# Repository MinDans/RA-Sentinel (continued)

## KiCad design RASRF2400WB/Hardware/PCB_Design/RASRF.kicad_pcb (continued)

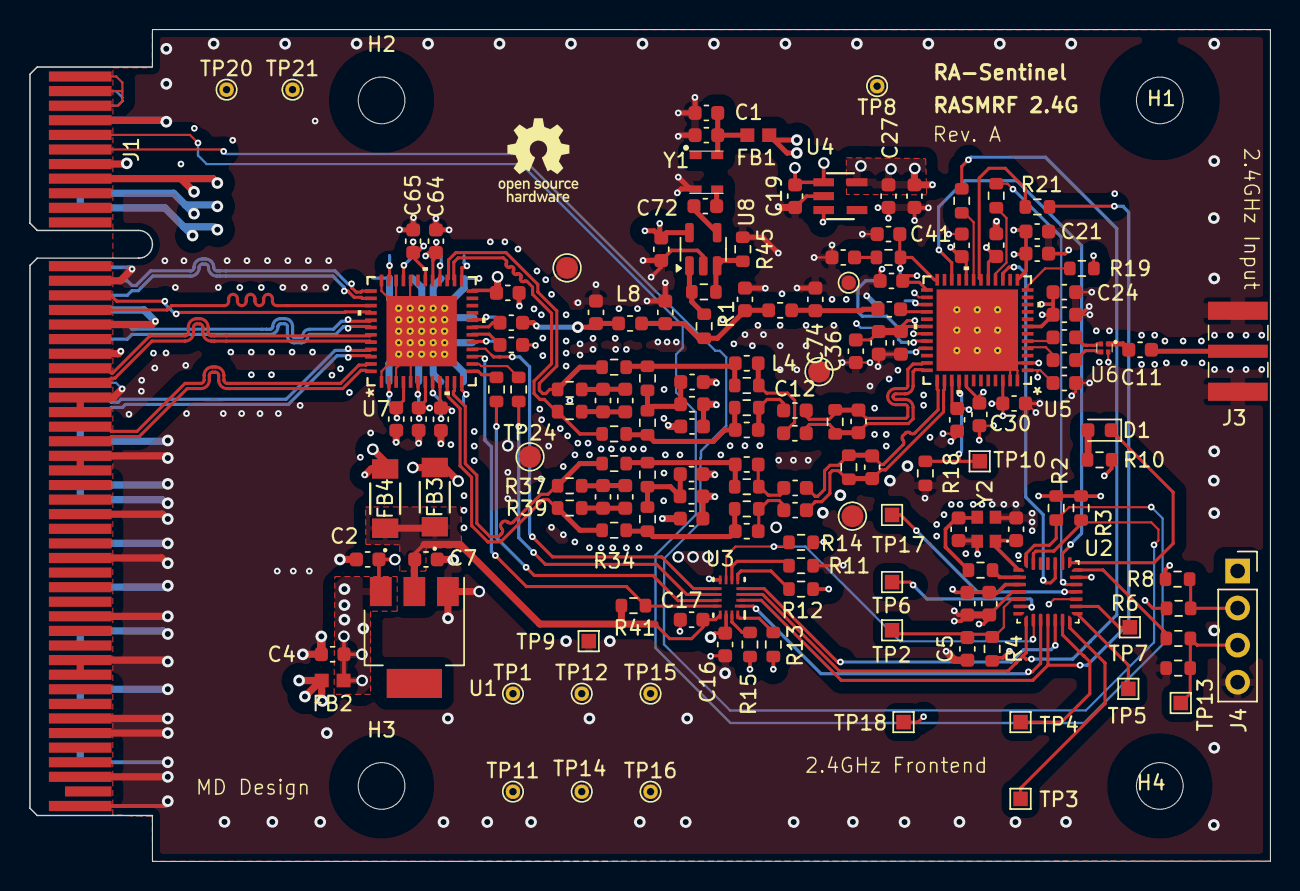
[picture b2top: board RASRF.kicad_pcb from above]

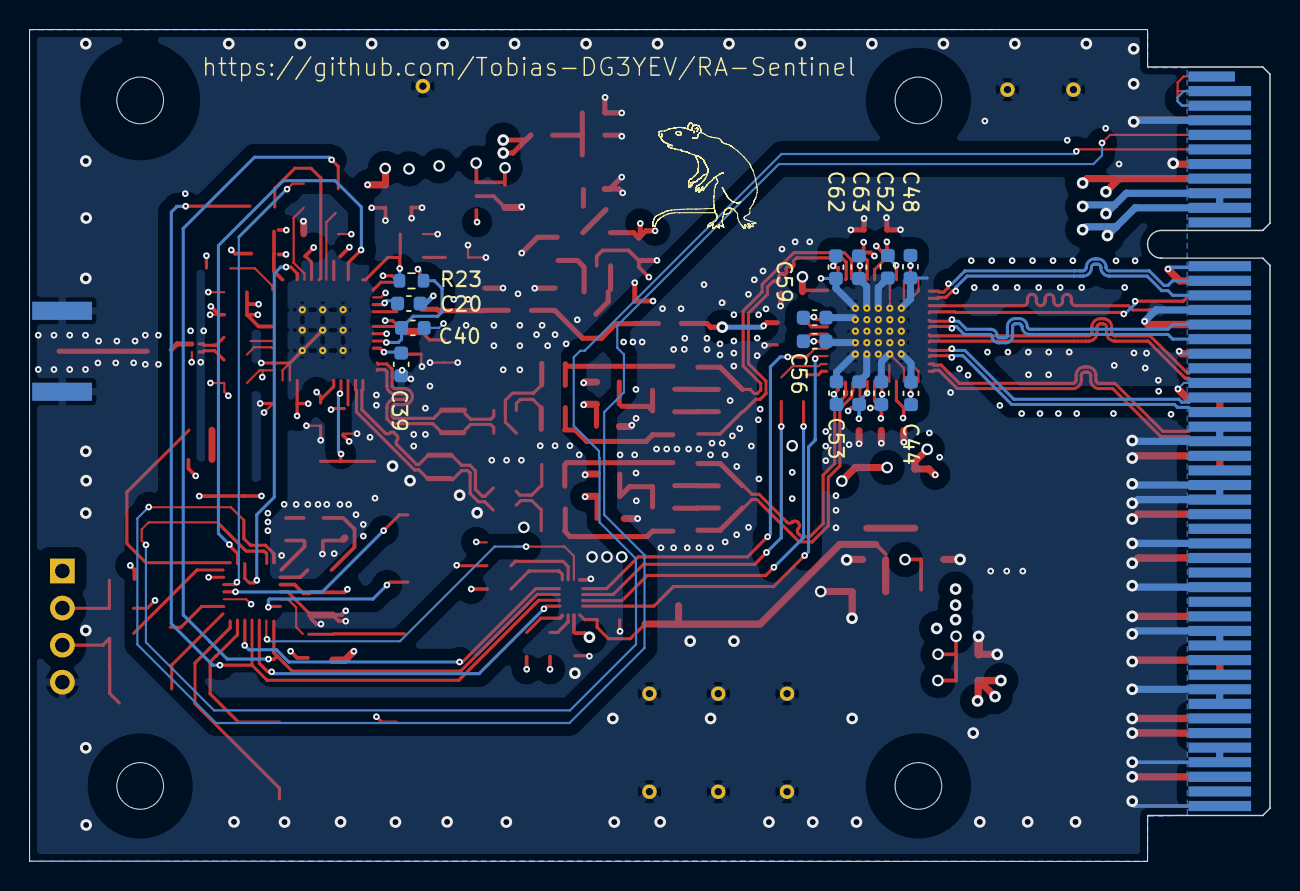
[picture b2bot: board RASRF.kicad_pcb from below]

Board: 4 copper layers, 85.0 x 57.0 mm, 176 parts (14 on the bottom side), 107 nets.

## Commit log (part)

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2026-04-13 Initial commit - RASRF2400WBMC Rev A.0 hardware design
2026-04-15 Update project maintainer name in README
2026-04-15 Correct naming and formatting in Design Notes
2026-04-15 Revise hardware description in documentation
    Updated hardware description for clarity and consistency.
2026-04-16 Rename Folder
2026-04-16 Fix PCB folder name and formatting in README
    Updated PCB design folder name and fixed formatting issues in the README.
2026-04-16 Dublicated - removed
2026-04-18 Fix board name formatting in README
2026-04-18 Fix link to RASBB README in documentation
    Updated the link to the RASBB README for improved accessibility.
2026-04-18 Remove NLnet funding acknowledgment from README
    Removed funding acknowledgment for NLnet from README.
2026-04-18 Update hardware description with component changes
2026-04-18 Fix typo in Design Notes for RASRF2400WB
2026-04-18 File Name Modification
2026-04-18 Add block diagram to Hardware Description
2026-04-18 Update Digaram
2026-04-19 Correct the U2 Regulator P/N
2026-04-19 Correct part number for LDO regulator
2026-04-25 Correct the MPN for a resistor/ Added NLNet and OSHW logos
2026-04-25 Added 2.4GHz Antenna Board
